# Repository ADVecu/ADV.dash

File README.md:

# ADV.dash

ADV.dash is a dashboard project built with **LVGL** and **ESP32-S3**.  
It is prepared to receive CAN bus data from **rusEFI** and, in the future, other programmable ECUs.

## Requirements
- PlatformIO
- ESP32-S3 DevKitC-1 board (1.5-inch display)
- LVGL library
- rusEFI CAN bus setup

## Compilation Steps
1. Clone the repository:
   ```bash
   git clone https://github.com/ADVecu/ADV.dash.git
   ```
2. Open the project in **PlatformIO**.
3. Copy the file `esp32-s3-devkitc-1-5inch` to the **boards** directory of the **Espressif** platform in PlatformIO.
4. Copy `lv_conf.h` to its correct LVGL configuration folder.
5. Build and upload the project to your ESP32-S3.

## Images

---

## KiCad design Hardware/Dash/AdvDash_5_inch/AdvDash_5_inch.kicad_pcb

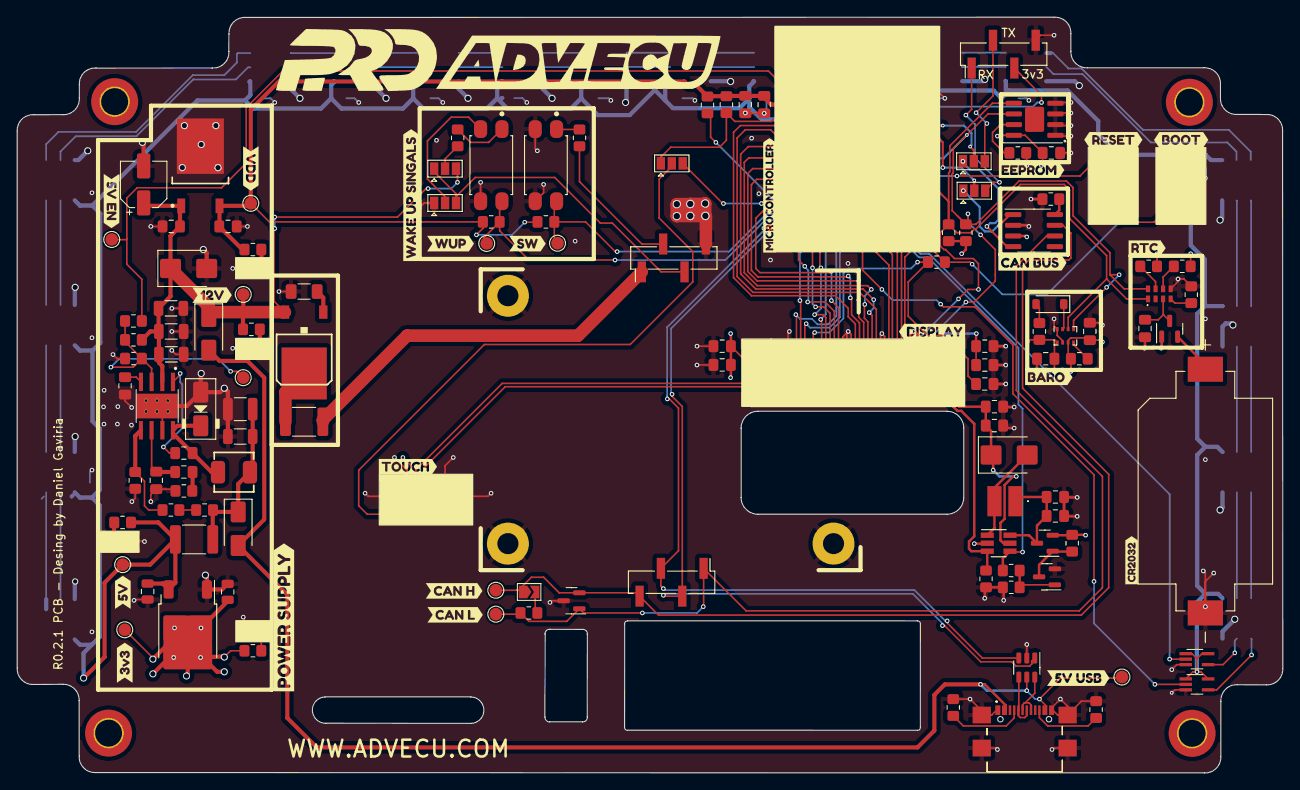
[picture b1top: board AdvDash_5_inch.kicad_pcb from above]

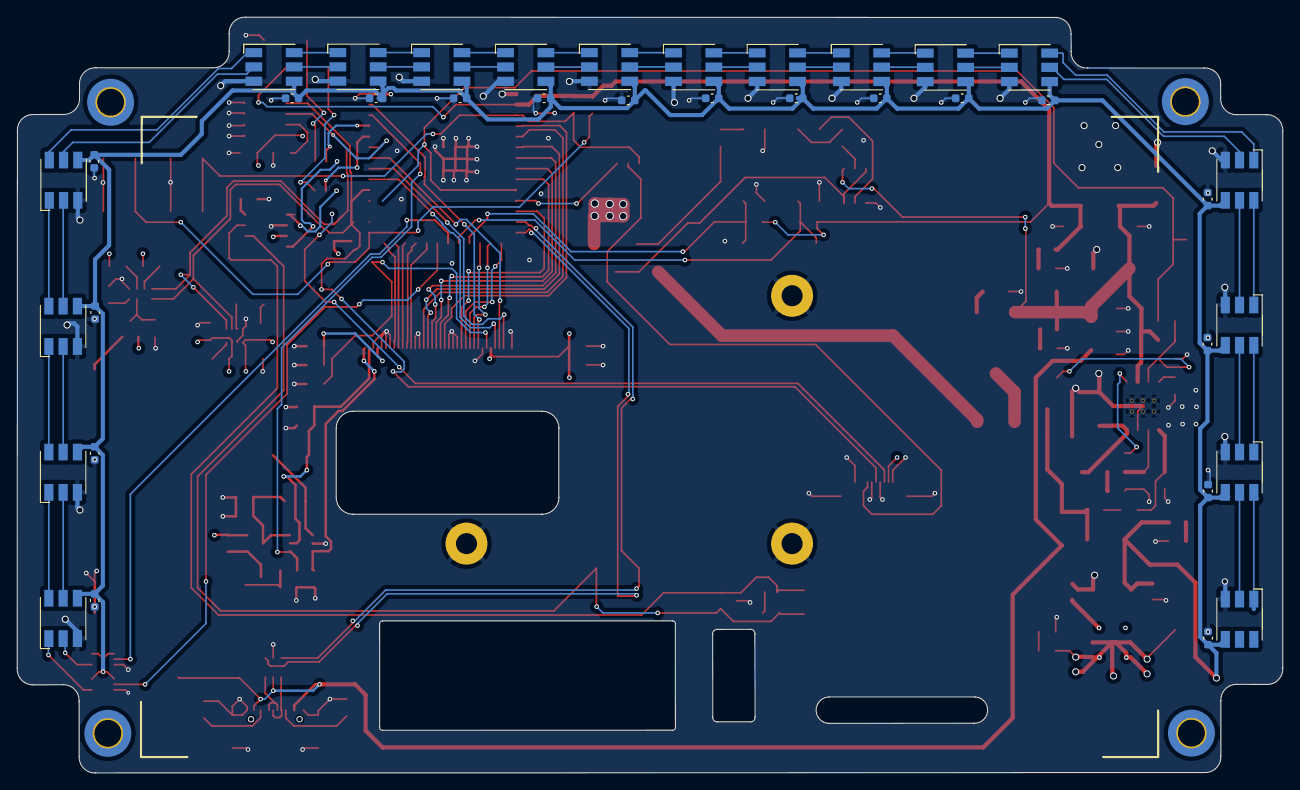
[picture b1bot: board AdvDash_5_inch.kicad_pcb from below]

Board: 4 copper layers, 150.6 x 89.9 mm, 188 parts (36 on the bottom side), 125 nets.

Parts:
BT1: CR2032-BS-6-1; BAT_CR2032-BS-6-1
C1, C7, C12, C21, C23, C27: 0.1uF; C_0805_2012Metric_Pad1.18x1.45mm_HandSolder
C2, C22, C24, C25: 10uF; C_0805_2012Metric_Pad1.18x1.45mm_HandSolder
C3, C4: 4.7uF; C_1206_3216Metric
C5: 10nF; C_1206_3216Metric
C6, C26: 10nF; C_0805_2012Metric_Pad1.18x1.45mm_HandSolder
C8: 4.7nF; C_0805_2012Metric_Pad1.18x1.45mm_HandSolder
C9: 39pF; C_0805_2012Metric_Pad1.18x1.45mm_HandSolder
C10: 33uF; C_1210_3225Metric
C11: 33uF; C_1206_3216Metric
C13: 100nF; CP_Elec_5x5.4
C14: 1uF - X7R; C_0805_2012Metric_Pad1.18x1.45mm_HandSolder
C15, C17: 22uF; C_0805_2012Metric_Pad1.18x1.45mm_HandSolder
C16, C20: 1uF; C_0805_2012Metric_Pad1.18x1.45mm_HandSolder
C18, C19: 100nF; C_0805_2012Metric_Pad1.18x1.45mm_HandSolder
C28, C29: 10uF; C_0805_2012Metric
C30, C31, C32, C33, C34, C35, C36, C37, C38, C39, C40, C41, C42, C43, C44, C45, C46, C47: 0.1uF; C_0603_1608Metric
D1, D11: 1N5819; D_SMA
D2: B340; D_SMA
D3, D4, D6, D12: LED; LED_0805_2012Metric_Pad1.15x1.40mm_HandSolder
D5: SMBJ20A; D_SMB
D7: SS24BF; D_SMB
D8: NUP2105L; SOT-23
D9: 1N4148W; D_SOD-123
D10: BAS70-05; SOT-23
D13, D14, D15, D16, D17, D18, D19, D20, D21, D22, D23, D24, D25, D26, D27, D28, D29, D30: SK9822; LED_RGB_5050-6
F1, F2: 3A 24V; Fuse_1812_4532Metric_Pad1.30x3.40mm_HandSolder
G1: TLF80511TF_V33; INF-PG-TO252-3-11_N
H1, H2, H3, H4: MountingHole; MountingHole_3.2mm_M3_DIN965_Pad_TopBottom
H5, H6, H7: MountingHole_Pad; MountingHole_2.5mm_Pad
IC1: RV-8803-C7; RV8803C7
IC2, IC3: 74HCT1G126GW,125; SOT-353_SC-70-5_Handsoldering
J1: 1-1734839-0; 117348390
J2: 54104-4031
J3: USB4110-GF-A; USB4110GFA
J4, J6: 2.54mm 1x4; PinHeader_1x04_P2.54mm_Vertical_SMD_Pin1Left
J5: UART0; PinHeader_1x04_P2.54mm_Vertical_SMD_Pin1Left
JP1: 120ohm; SolderJumper-2_P1.3mm_Open_TrianglePad1.0x1.5mm
JP2, JP3, JP4, JP6: ACT +/-; SolderJumper-3_P1.3mm_Open_Pad1.0x1.5mm
JP5: Reset Control; SolderJumper-3_P1.3mm_Open_Pad1.0x1.5mm
L1: 6.8uH; MDA4020-6R8M
L2: 6.8uH; TCK145
Q2: AO3401A; SOT-23
Q3: S8050; SOT-23
R1, R2, R7, R12, R17, R24, R26, R27, R35, R36: 10K; R_0805_2012Metric_Pad1.20x1.40mm_HandSolder
R3: 332k; R_0805_2012Metric_Pad1.20x1.40mm_HandSolder
R4: 68k1; R_0805_2012Metric_Pad1.20x1.40mm_HandSolder
R5: 49k9; R_0805_2012Metric_Pad1.20x1.40mm_HandSolder
R6, R10, R21: 0R; R_0805_2012Metric_Pad1.20x1.40mm_HandSolder
R8: 1k91; R_0805_2012Metric_Pad1.20x1.40mm_HandSolder
R9: 2K7; R_1206_3216Metric_Pad1.30x1.75mm_HandSolder
R13, R14: 1k3; R_0805_2012Metric_Pad1.20x1.40mm_HandSolder
R15: 10R; R_0805_2012Metric_Pad1.20x1.40mm_HandSolder
R16, R28, R29, R30, R31: 100k; R_0805_2012Metric_Pad1.20x1.40mm_HandSolder
R18: 100R; R_0805_2012Metric_Pad1.20x1.40mm_HandSolder
R19, R20: 4.7k; R_0805_2012Metric_Pad1.20x1.40mm_HandSolder
R22, R23: 5k1; R_0805_2012Metric_Pad1.20x1.40mm_HandSolder
R25: 120; R_0805_2012Metric_Pad1.20x1.40mm_HandSolder
R32: 2k; R_0805_2012Metric_Pad1.20x1.40mm_HandSolder
R33, R34: 2K7; R_0805_2012Metric_Pad1.20x1.40mm_HandSolder
SW1, SW2: RESET; SW_TL3342F160QG_TR
T1: IRFR5305; D-PAK_TO252AA
TP1: VIN_TP; TestPoint_Pad_D1.5mm
TP2: EN_TP; TestPoint_Pad_D1.5mm
TP3: EN_MCU_TP; TestPoint_Pad_D1.5mm
TP4: USB_5VTP; TestPoint_Pad_D1.5mm
TP5: 5V_TP; TestPoint_Pad_D1.5mm
TP6: VDD_TP; TestPoint_Pad_D1.5mm
TP7: 3.3V_TP; TestPoint_Pad_D1.5mm
TP8: WAKE_UP_TP; TestPoint_Pad_D1.5mm
TP9: SW12V_TP; TestPoint_Pad_D1.5mm
TP10: CANH_TP; TestPoint_Pad_D1.5mm
TP11: CANL_TP; TestPoint_Pad_D1.5mm
U1: ESP32-S3-WROOM-1-N4R8; ESP32-S3-WROOM-1
U2: TPS54331DDA; CONV_TPS54331DDA
U3: MT9201; SOT-23-6_Handsoldering
U4: USBLC6-2P6; SOT-23-6
U5: SN65HVD230; SOIC-8_3.9x4.9mm_P1.27mm
U6: BMP280; Bosch_LGA-8_2x2.5mm_P0.65mm_ClockwisePinNumbering
U7: CAT24C51; SOIC-8-1EP_3.9x4.9mm_P1.27mm_EP2.29x3mm
U8: LD1086DT33TR; TO-252-2
U9, U10: PC817; SOIC254P975X460-4N
kibuzzard-653B3D6F: G***; kibuzzard-653B3D6F
kibuzzard-653B3D82: G***; kibuzzard-653B3D82
kibuzzard-653B3DF4: G***; kibuzzard-653B3DF4
kibuzzard-653B3E73: G***; kibuzzard-653B3E73
kibuzzard-653B3E80: G***; kibuzzard-653B3E80
kibuzzard-653B3ED4: G***; kibuzzard-653B3ED4
kibuzzard-653B3EE1: G***; kibuzzard-653B3EE1
kibuzzard-653B3EFA: G***; kibuzzard-653B3EFA
kibuzzard-653B3F30: G***; kibuzzard-653B3F30
kibuzzard-653B3F43: G***; kibuzzard-653B3F43
kibuzzard-653B3FA3: G***; kibuzzard-653B3FA3
kibuzzard-653B3FD4: G***; kibuzzard-653B3FD4
kibuzzard-653B40B3: G***; kibuzzard-653B40B3
kibuzzard-653B41DD: G***; kibuzzard-653B41DD
kibuzzard-653B42DB: G***; kibuzzard-653B42DB
kibuzzard-653B414E: G***; kibuzzard-653B414E
kibuzzard-653B423C: G***; kibuzzard-653B423C
kibuzzard-653B435E: G***; kibuzzard-653B435E
kibuzzard-653B445A: G***; kibuzzard-653B445A
kibuzzard-653B4004: G***; kibuzzard-653B4004
kibuzzard-653B4099: G***; kibuzzard-653B4099
kibuzzard-653B4196: G***; kibuzzard-653B4196

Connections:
+3.3V: C19.1, C20.1, C22.1, C23.1, C24.1, C25.1, C27.2, C29.1, D10.1 (A2), J1.2, J2.10, J2.37, Q2.2 (S), R13.2, R16.1, R19.1, R20.2, R26.2, R27.2, R29.1, R30.1, TP7.1, U5.3 (VCC), U6.6 (VDDIO), U6.8 (VDD), U7.8 (VCC), U8.2 (OUT)
+5V: C28.1, C30.2, C31.2, C32.2, C33.2, C34.2, C35.2, C36.2, C37.2, C38.2, C39.2, C40.2, C41.2, C42.2, C43.2, C44.2, C45.2, C46.2, C47.2, D13.4 (VCC), D14.4 (VCC), D15.4 (VCC), D16.4 (VCC), D17.4 (VCC), D18.4 (VCC), D19.4 (VCC), D20.4 (VCC), D21.4 (VCC), D22.4 (VCC), D23.4 (VCC), D24.4 (VCC), D25.4 (VCC), D26.4 (VCC), D27.4 (VCC), D28.4 (VCC), D29.4 (VCC), D30.4 (VCC), F1.2, IC2.1 (OE), IC2.5 (VCC), IC3.1 (OE), IC3.5 (VCC), R32.2, TP5.1, U8.3 (IN)
/CAN_H: D8.2 (K), J4.4, JP1.1 (A), TP10.1, U5.7 (CANH)
/CAN_L: D8.1 (K), J4.1, R25.1, TP11.1, U5.6 (CANL)
/Can Bus/CRX: JP4.1 (A), U5.4 (R)
/Can Bus/CTX: JP6.1 (A), U5.1 (D)
/Connector/SW_12V: J6.2, R34.1
/Connector/WAKE_UP: J6.3, JP2.1 (A), JP3.3 (B)
/Display/B3: J2.17, U1.12 (GPIO8/TOUCH8/ADC1_CH7/SUBSPICS1)
/Display/B4: J2.16, U1.15 (GPIO3/TOUCH3/ADC1_CH2)
/Display/B5: J2.15, U1.16 (GPIO46)
/Display/B6: J2.14, U1.17 (GPIO9/TOUCH9/ADC1_CH8/FSPIHD/SUBSPIHD)
/Display/B7: J2.13, U1.39 (GPIO1/TOUCH1/ADC1_CH0)
/Display/DCLK: R2.1, R21.2, SW2.1, SW2.2, U1.27 (GPIO0/BOOT)
/Display/DE: J2.7, U1.33 (MTDO/GPIO40/CLK_OUT2)
/Display/G2: J2.26, U1.5 (GPIO5/TOUCH5/ADC1_CH4)
/Display/G3: J2.25, U1.6 (GPIO6/TOUCH6/ADC1_CH5)
/Display/G4: J2.24, U1.7 (GPIO7/TOUCH7/ADC1_CH6)
/Display/G5: J2.23, U1.8 (GPIO15/U0RTS/ADC2_CH4/XTAL_32K_P)
/Display/G6: J2.22, U1.9 (GPIO16/U0CTS/ADC2_CH5/XTAL_32K_N)
/Display/G7: J2.21, U1.4 (GPIO4/TOUCH4/ADC1_CH3)
/Display/HSYNC: J2.9, U1.32 (MTCK/GPIO39/CLK_OUT3/SUBSPICS1)
/Display/LCD_BL_CTR: R18.1, U1.38 (GPIO2/TOUCH2/ADC1_CH1), U3.4 (EN)
/Display/LCD_LEDA: C17.1, C18.1, D7.1 (K), J2.39, U3.5 (OV)
/Display/LCD_LEDK: J2.40, R15.2, U3.3 (FB)
/Display/R3: J2.33, U1.26 (GPIO45)
/Display/R4: J2.32, U1.25 (GPIO48/SPICLK_N/SUBSPICLK_N_DIFF)
/Display/R5: J2.31, U1.24 (GPIO47/SPICLK_P/SUBSPICLK_P_DIFF)
/Display/R6: J2.30, U1.23 (GPIO21)
/Display/R7: J2.29, U1.22 (GPIO14/TOUCH14/ADC2_CH3/FSPIWP/FSPIDQS/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)
/Display/TP_RST: JP5.1 (A), R1.1, SW1.1, SW1.2, U1.3 (EN)
/Display/TP_RST_2: JP5.3 (B), U1.11 (GPIO18/U1RXD/ADC2_CH7/CLK_OUT3)
/Display/VSYNC: J2.8, U1.34 (MTDI/GPIO41/CLK_OUT1)
/LEDs/WLED_CLK: IC2.2 (A), U1.20 (GPIO12/TOUCH12/ADC2_CH1/FSPICLK/FSPIIO6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)
/LEDs/WLED_CRT: IC3.2 (A), U1.21 (GPIO13/TOUCH13/ADC2_CH2/FSPIQ/FSPIIO7/S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)
/MCU/5V_EN: R10.1, TP3.1, U1.10 (GPIO17/U1TXD/ADC2_CH6)
/MCU/SW_12V: R36.1, TP9.1, U1.18 (GPIO10/TOUCH10/ADC1_CH9/FSPICS0/FSPIIO4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), U10.4
/MCU/U0RXD: J5.1, JP6.3 (B)
/MCU/U0TXD: J5.2, JP4.3 (B)
/MCU/WAKE_UP: R35.1, TP8.1, U1.19 (GPIO11/TOUCH11/ADC2_CH0/FSPID/FSPIIO5/S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), U9.4
/Power Supply/VIN/15_PROT: C3.1, C4.1, C5.1, C12.2, C13.1, D5.1 (K), D11.1 (K), G1.1 (I), JP2.3 (B), R3.1, R12.2, T1.3, TP1.1, U2.2 (VIN)
/SCL: IC1.8 (SCL), J1.3, R19.2, U1.35 (MTMS/GPIO42), U6.4 (SCK), U7.6 (SCL)
/SDA: IC1.1 (SDA), J1.5, R20.1, U1.31 (GPIO38/FSPIWP/SUBSPIWP), U6.3 (SDI), U7.5 (SDA)
/USB5V: D1.2 (A), D11.2 (A), J3.A4 (VBUS), J3.A9 (VBUS), J3.B4 (VBUS), J3.B9 (VBUS), TP4.1, U4.5 (VBUS)
/USBC/D+: J3.A6 (Dp1), J3.B6 (Dp2), J4.2, U1.14 (GPIO20/U1CTS/ADC2_CH9/CLK_OUT1/USB_D+), U4.1 (I/O1), U4.6 (I/O1)
/USBC/D-: J3.A7 (Dn1), J3.B7 (Dn2), J4.3, U1.13 (GPIO19/U1RTS/ADC2_CH8/CLK_OUT2/USB_D-), U4.3 (I/O2), U4.4 (I/O2)
/VIN15: F2.2, J6.1
GND: BT1.N, C1.2, C2.2, C3.2, C4.2, C5.2, C6.2, C9.2, C10.2, C11.2, C12.1, C13.2, C14.2, C15.2, C16.2, C17.2, C18.2, C19.2, C20.2, C21.2, C22.2, C23.2, C24.2, C25.2, C26.2, C27.1, C28.2, C29.2, C30.1, C31.1, C32.1, C33.1, C34.1, C35.1, C36.1, C37.1, C38.1, C39.1, C40.1, C41.1, C42.1, C43.1, C44.1, C45.1, C46.1, C47.1, D2.2 (A), D3.1 (K), D4.1 (K), D5.2 (A), D6.1 (K), D8.3 (A), D12.1 (K), D13.3 (GND), D14.3 (GND), D15.3 (GND), D16.3 (GND), D17.3 (GND), D18.3 (GND), D19.3 (GND), D20.3 (GND), D21.3 (GND), D22.3 (GND), D23.3 (GND), D24.3 (GND), D25.3 (GND), D26.3 (GND), D27.3 (GND), D28.3 (GND), D29.3 (GND), D30.3 (GND), G1.2 (GND), H5.1, H6.1, H7.1, IC1.5 (VSS), IC2.3 (GND), IC3.3 (GND), J1.1, J1.4, J1.6, J1.10, J1.MP1, J1.MP2, J2.5, J2.12, J2.18, J2.19, J2.20, J2.27, J2.28, J2.34, J2.35, J2.36, J2.38, J3.A1 (GND), J3.A12 (GND), J3.B1 (GND), J3.B12 (GND), J3.MP1, J3.MP2, J3.MP3, J3.MP4, J5.4, J6.4, JP3.1 (A), Q3.2 (E), R4.2, R5.2, R8.2, R9.2, R15.1, R17.2, R22.1, R23.2, R24.1, R28.2, R31.2, SW1.3, SW1.4, SW2.3, SW2.4, U1.1 (GND), U1.40 (GND), U1.41 (GND), U2.7 (GND), U2.9 (POWERPAD), U2.10 (GND), U2.11 (GND), U2.12 (GND), U2.13 (GND), U2.14 (GND), U2.15 (GND), U3.2 (GND), U4.2 (GND), U5.2 (GND), U6.1 (GND), U6.7 (GND), U7.1 (A0), U7.2 (A1), U7.3 (A2), U7.4 (GND), U8.1 (ADJ/GND), U9.3, U10.2, U10.3
unnamed: C8.2, R5.1
unnamed: C21.1, J2.11, R21.1
unnamed: C10.1, C11.1, D1.1 (K), F1.1, L1.2, R6.1
unnamed: C7.2, D2.1 (K), L1.1, U2.8 (PH)
unnamed: D3.2 (A), R12.1
unnamed: D4.2 (A), R13.1
unnamed: D6.2 (A), R14.1
unnamed: D7.2 (A), L2.2, U3.1 (SW)
unnamed: D9.2 (A), R26.1
unnamed: D9.1 (K), U6.2 (CSB)
unnamed: BT1.P, D10.2 (A1)
unnamed: C26.1, D10.3 (K), IC1.3 (VDD)
unnamed: D12.2 (A), R32.1
unnamed: D13.2 (CI), IC2.4 (Y)
unnamed: D13.5 (CO), D14.2 (CI)
unnamed: D13.1 (DI), IC3.4 (Y)
unnamed: D13.6 (DO), D14.1 (DI)
unnamed: D14.5 (CO), D15.2 (CI)
unnamed: D14.6 (DO), D15.1 (DI)
unnamed: D15.5 (CO), D16.2 (CI)
unnamed: D15.6 (DO), D16.1 (DI)
unnamed: D16.5 (CO), D17.2 (CI)
unnamed: D16.6 (DO), D17.1 (DI)
unnamed: D17.5 (CO), D18.2 (CI)
unnamed: D17.6 (DO), D18.1 (DI)
unnamed: D18.5 (CO), D19.2 (CI)
unnamed: D18.6 (DO), D19.1 (DI)
unnamed: D19.5 (CO), D20.2 (CI)
unnamed: D19.6 (DO), D20.1 (DI)
unnamed: D20.5 (CO), D21.2 (CI)
unnamed: D20.6 (DO), D21.1 (DI)
unnamed: D21.5 (CO), D22.2 (CI)
unnamed: D21.6 (DO), D22.1 (DI)
unnamed: D22.5 (CO), D23.2 (CI)
unnamed: D22.6 (DO), D23.1 (DI)
unnamed: D23.5 (CO), D24.2 (CI)
unnamed: D23.6 (DO), D24.1 (DI)
unnamed: D24.5 (CO), D25.2 (CI)
unnamed: D24.6 (DO), D25.1 (DI)
unnamed: D25.5 (CO), D26.2 (CI)
unnamed: D25.6 (DO), D26.1 (DI)
unnamed: D26.5 (CO), D27.2 (CI)
unnamed: D26.6 (DO), D27.1 (DI)
unnamed: D27.5 (CO), D28.2 (CI)
unnamed: D27.6 (DO), D28.1 (DI)
unnamed: D28.5 (CO), D29.2 (CI)
unnamed: D28.6 (DO), D29.1 (DI)
unnamed: D29.5 (CO), D30.2 (CI)
unnamed: D29.6 (DO), D30.1 (DI)
unnamed: F2.1, T1.4
unnamed: IC1.4 (CLKOE), R28.1
unnamed: IC1.7 (EVI), R29.2
unnamed: IC1.6 (~INT), R30.2
unnamed: J3.A5 (CC1), R22.2
unnamed: J3.B5 (CC2), R23.1
unnamed: JP1.2 (B), R25.2
unnamed: JP2.2 (C), R33.1
unnamed: JP3.2 (C), U9.2
unnamed: JP4.2 (C), U1.37 (U0TXD/GPIO43/CLK_OUT1)
unnamed: J1.7, JP5.2 (C)
unnamed: JP6.2 (C), U1.36 (U0RXD/GPIO44/CLK_OUT2)
unnamed: C15.1, C16.1, L2.1, Q2.3 (D), U3.6 (VIN)
unnamed: Q2.1 (G), Q3.3 (C), R16.2
unnamed: Q3.1 (B), R17.1, R18.2
unnamed: R6.2, R7.1
unnamed: R9.1, T1.1
unnamed: R33.2, U9.1
unnamed: R34.2, U10.1
unnamed: C7.1, U2.1 (BOOT)
unnamed: C8.1, C9.1, U2.6 (COMP)
unnamed: R3.2, R4.1, R10.2, TP2.1, U2.3 (EN)
unnamed: C6.1, U2.4 (SS)
unnamed: R7.2, R8.1, U2.5 (VSENSE)
unnamed: R24.2, U5.8 (Rs)
unnamed: R27.1, U6.5 (SDO)
unnamed: R31.1, U7.7 (WP)
VDD: C1.1, C2.1, C14.1, G1.3 (Q), J5.3, R1.2, R2.2, R14.2, R35.2, R36.2, TP6.1, U1.2 (3V3)

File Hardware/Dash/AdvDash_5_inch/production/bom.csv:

Designator,Footprint,Quantity,Value,LCSC Part #
BT1,BAT_CR2032-BS-6-1,1,CR2032-BS-6-1,C70377
"C1, C12, C21, C23, C27, C7",0805,6,0.1uF,C38141
C10,1210,1,33uF,C531418
C11,1206,1,33uF,C342606
C13,CP_Elec_5x5.4,1,100nF,C2992591
C14,0805,1,1uF - X7R,C116352
"C15, C17",0805,2,22uF,C602037
"C16, C20",0805,2,1uF,C28323
"C18, C19",0805,2,100nF,C38141
"C2, C22, C24, C25",0805,4,10uF,C15850
"C26, C6",0805,2,10nF,C83170
"C28, C29",0805,2,10uF,C1713
"C3, C4",1206,2,4.7uF,C1872
"C30, C31, C32, C33, C34, C35, C36, C37, C38, C39, C40, C41, C42, C43, C44, C45, C46, C47",0603,18,0.1uF,C577419
C5,1206,1,10nF,C106239
C8,0805,1,4.7nF,C1744
C9,0805,1,39pF,C1817
"D1, D11",D_SMA,2,1N5819,C437199
D10,SOT-23,1,BAS70-05,C5189799
D12,0805,1,LED,C965819
"D13, D14, D15, D16, D17, D18, D19, D20, D21, D22, D23, D24, D25, D26, D27, D28, D29, D30",LED_RGB_5050-6,18,SK9822,C2829089
D2,D_SMA,1,B340,C64982
"D3, D4",0805,2,LED,C965818
D5,D_SMB,1,SMBJ20A,C151257
D6,0805,1,LED,C965812
D7,D_SMB,1,SS24BF,C35501
D8,SOT-23,1,NUP2105L,C5158054
D9,D_SOD-123,1,1N4148W,C5345962
"F1, F2",1812,2,3A 24V,C883154
G1,INF-PG-TO252-3-11_N,1,TLF80511TF_V33,
"H1, H2, H3, H4",MountingHole_3.2mm_M3_DIN965_Pad_TopBottom,4,MountingHole,
"H5, H6, H7",MountingHole_2.5mm_Pad,3,MountingHole_Pad,C3020128
IC1,RV8803C7,1,RV-8803-C7,C2846926
"IC2, IC3",SOT-353_SC-70-5_Handsoldering,2,"74HCT1G126GW,125",C455064
J1,117348390,1,1-1734839-0,C590935
J2,54104-4031,1,54104-4031,C164172
J3,USB4110GFA,1,USB4110-GF-A,
"J4, J6",PinHeader_1x04_P2.54mm_Vertical_SMD_Pin1Left,2,2.54mm 1x4,
J5,PinHeader_1x04_P2.54mm_Vertical_SMD_Pin1Left,1,UART0,
JP1,SolderJumper-2_P1.3mm_Open_TrianglePad1.0x1.5mm,1,120ohm,
"JP2, JP3, JP4, JP6",SolderJumper-3_P1.3mm_Open_Pad1.0x1.5mm,4,ACT +/-,
JP5,SolderJumper-3_P1.3mm_Open_Pad1.0x1.5mm,1,Reset Control,
L1,MDA4020-6R8M,1,6.8uH,C2847472
L2,TCK145,1,6.8uH,C167253
Q2,SOT-23,1,AO3401A,C15127
Q3,SOT-23,1,S8050,C266592
"R1, R12, R17, R2, R24, R26, R27, R35, R36, R7",0805,10,10K,C17414
R10,0805,1,0R,C17414
"R13, R14",0805,2,1k3,C2933303
R15,0805,1,10R,C25278
"R16, R28, R29, R30, R31",0805,5,100k,C149504
R18,0805,1,100R,C17408
"R19, R20",0805,2,4.7k,C17673
"R21, R6",0805,2,0R,C17477
"R22, R23",0805,2,5k1,C84375
R25,0805,1,120,C114245
R3,0805,1,332k,C212383
R32,0805,1,2k,C17604
"R33, R34",0805,2,2K7,C17530
R4,0805,1,68k1,C5266070
R5,0805,1,49k9,C17719
R8,0805,1,1k91,C2999452
R9,1206,1,2K7,C2907449
"SW1, SW2",SW_TL3342F160QG_TR,2,RESET,C2886898
T1,D-PAK_TO252AA,1,IRFR5305,C5155388
TP1,TestPoint_Pad_D1.5mm,1,VIN_TP,
TP10,TestPoint_Pad_D1.5mm,1,CANH_TP,
TP11,TestPoint_Pad_D1.5mm,1,CANL_TP,
TP2,TestPoint_Pad_D1.5mm,1,EN_TP,
TP3,TestPoint_Pad_D1.5mm,1,EN_MCU_TP,
TP4,TestPoint_Pad_D1.5mm,1,USB_5VTP,
TP5,TestPoint_Pad_D1.5mm,1,5V_TP,
TP6,TestPoint_Pad_D1.5mm,1,VDD_TP,
TP7,TestPoint_Pad_D1.5mm,1,3.3V_TP,
TP8,TestPoint_Pad_D1.5mm,1,WAKE_UP_TP,
TP9,TestPoint_Pad_D1.5mm,1,SW12V_TP,
U1,ESP32-S3-WROOM-1,1,ESP32-S3-WROOM-1-N4R8,C2913200
"U10, U9",SOIC254P975X460-4N,2,PC817,C3025164
U2,CONV_TPS54331DDA,1,TPS54331DDA,C90761
U3,SOT-23-6_Handsoldering,1,MT9201,C182966
U4,SOT-23-6,1,USBLC6-2P6,C7519
U5,SOIC-8_3.9x4.9mm_P1.27mm,1,SN65HVD230,C12084
U6,Bosch_LGA-8_2x2.5mm_P0.65mm_ClockwisePinNumbering,1,BMP280,C83291
U7,SOIC-8-1EP_3.9x4.9mm_P1.27mm_EP2.29x3mm,1,CAT24C51,C79986
U8,TO-252-2,1,LD1086DT33TR,C12051

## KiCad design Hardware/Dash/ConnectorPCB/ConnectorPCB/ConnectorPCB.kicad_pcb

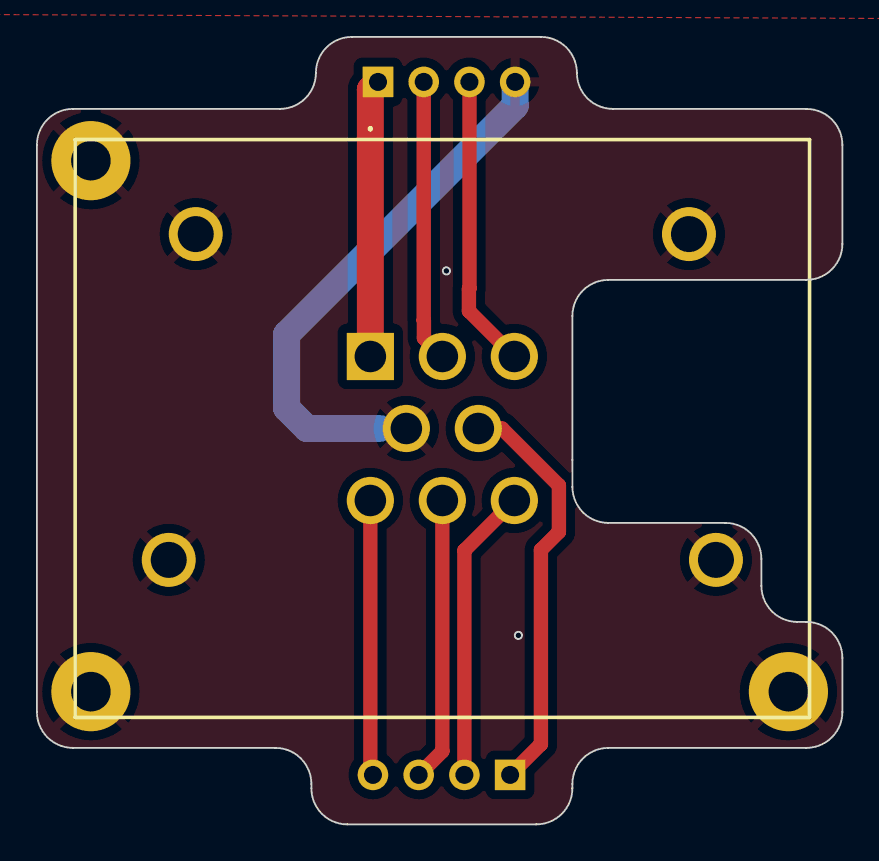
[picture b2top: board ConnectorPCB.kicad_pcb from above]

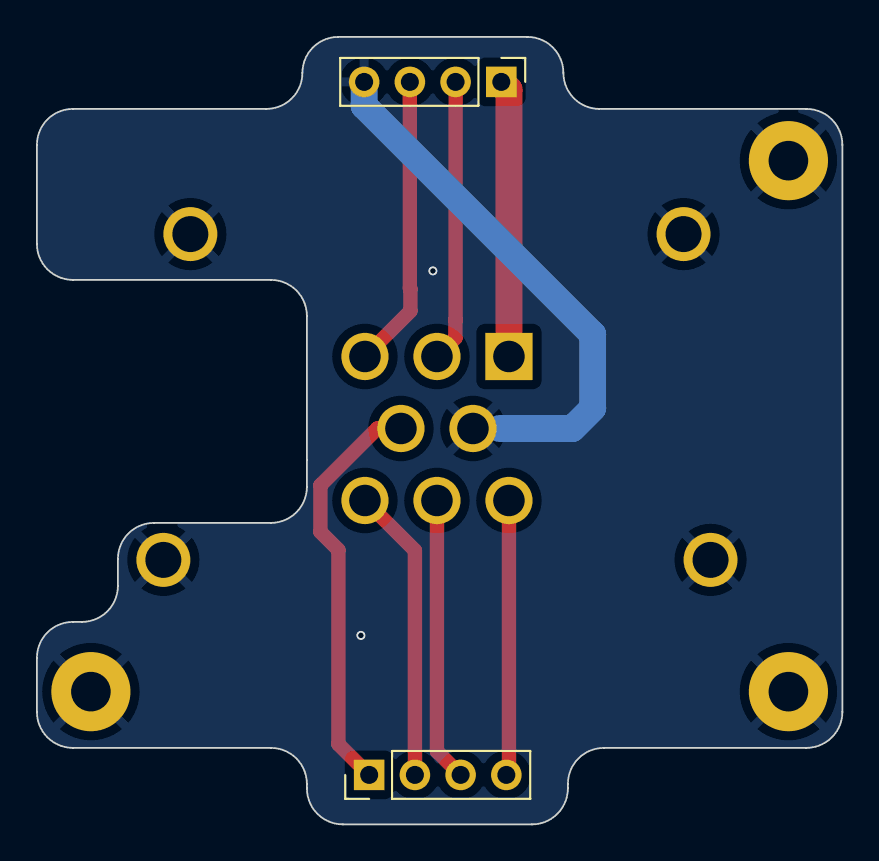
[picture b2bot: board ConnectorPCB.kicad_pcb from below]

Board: 2 copper layers, 44.8 x 43.8 mm, 4 parts (2 on the bottom side), 8 nets.

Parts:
H5: MountingHole_Pad; MountingHole_2.2mm_M2_Pad
J1: 776276-1; 7762761
J2, J3: 2.54mm 1x4; PinHeader_1x04_P2.54mm_Vertical

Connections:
CAN_H: J1.6, J3.4
CAN_L: J1.5, J3.1
D+: J1.7, J3.3
D-: J1.8, J3.2
GND: H5.1, J1.4, J1.MH1, J1.MH2, J1.MH3, J1.MH4, J2.4
SW_12V: J1.2, J2.2
VIN/15V: J1.1, J2.1
WAKE_UP: J1.3, J2.3

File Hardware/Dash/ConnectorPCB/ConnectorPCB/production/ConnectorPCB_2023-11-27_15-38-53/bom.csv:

Designator,Footprint,Quantity,Value,LCSC Part #
J1,7762761,1,776276-1,
"J2, J3",PinHeader_1x04_P2.54mm_Vertical,2,2.54mm 1x4,

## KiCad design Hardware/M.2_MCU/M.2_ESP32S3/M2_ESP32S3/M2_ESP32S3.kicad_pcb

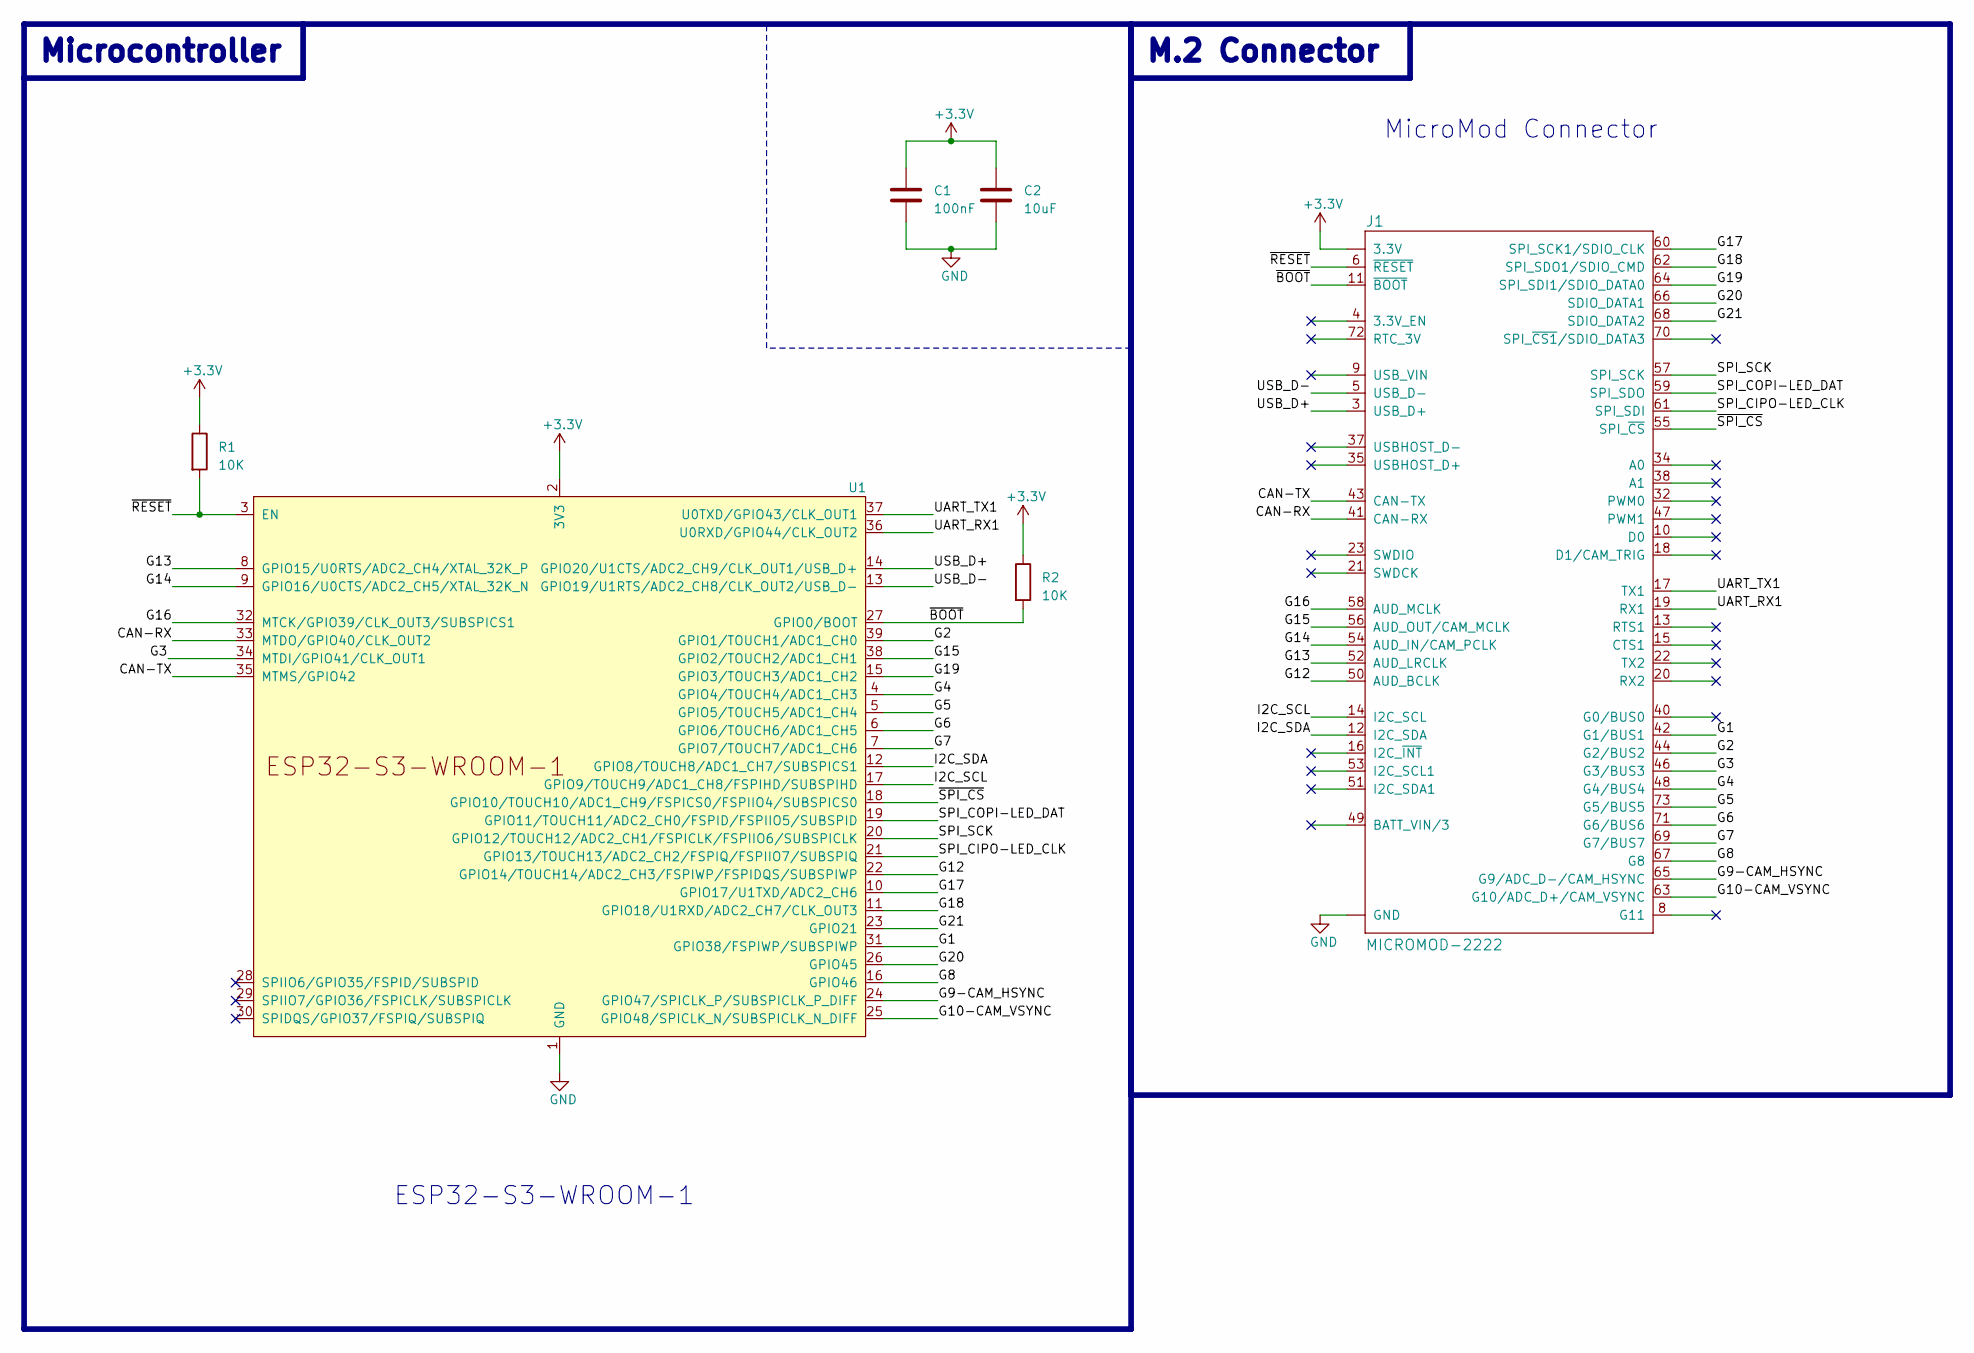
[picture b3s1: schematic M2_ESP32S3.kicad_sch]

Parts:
C1: 100nF; C_0805_2012Metric_Pad1.18x1.45mm_HandSolder
C2: 10uF; C_0805_2012Metric_Pad1.18x1.45mm_HandSolder
J1: MICROMOD-2222; M.2-CARD-E-22
R1, R2: 10K; R_0805_2012Metric_Pad1.15x1.40mm_HandSolder
U1: ESP32-S3-WROOM-1

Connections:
+3.3V: C1.1, C2.1, J1.2 (3.3V), J1.74 (3.3V), R1.1, R2.1, U1.2 (3V3)
/CAN-RX: J1.41 (CAN-RX), U1.33 (MTDO/GPIO40/CLK_OUT2)
/CAN-TX: J1.43 (CAN-TX), U1.35 (MTMS/GPIO42)
/G1: J1.42 (G1/BUS1), U1.31 (GPIO38/FSPIWP/SUBSPIWP)
/G2: J1.44 (G2/BUS2), U1.39 (GPIO1/TOUCH1/ADC1_CH0)
/G3: J1.46 (G3/BUS3), U1.34 (MTDI/GPIO41/CLK_OUT1)
/G4: J1.48 (G4/BUS4), U1.4 (GPIO4/TOUCH4/ADC1_CH3)
/G5: J1.73 (G5/BUS5), U1.5 (GPIO5/TOUCH5/ADC1_CH4)
/G6: J1.71 (G6/BUS6), U1.6 (GPIO6/TOUCH6/ADC1_CH5)
/G7: J1.69 (G7/BUS7), U1.7 (GPIO7/TOUCH7/ADC1_CH6)
/G8: J1.67 (G8), U1.16 (GPIO46)
/G9-CAM_HSYNC: J1.65 (G9/ADC_D-/CAM_HSYNC), U1.24 (GPIO47/SPICLK_P/SUBSPICLK_P_DIFF)
/G10-CAM_VSYNC: J1.63 (G10/ADC_D+/CAM_VSYNC), U1.25 (GPIO48/SPICLK_N/SUBSPICLK_N_DIFF)
/G12: J1.50 (AUD_BCLK), U1.22 (GPIO14/TOUCH14/ADC2_CH3/FSPIWP/FSPIDQS/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)
/G13: J1.52 (AUD_LRCLK), U1.8 (GPIO15/U0RTS/ADC2_CH4/XTAL_32K_P)
/G14: J1.54 (AUD_IN/CAM_PCLK), U1.9 (GPIO16/U0CTS/ADC2_CH5/XTAL_32K_N)
/G15: J1.56 (AUD_OUT/CAM_MCLK), U1.38 (GPIO2/TOUCH2/ADC1_CH1)
/G16: J1.58 (AUD_MCLK), U1.32 (MTCK/GPIO39/CLK_OUT3/SUBSPICS1)
/G17: J1.60 (SPI_SCK1/SDIO_CLK), U1.10 (GPIO17/U1TXD/ADC2_CH6)
/G18: J1.62 (SPI_SDO1/SDIO_CMD), U1.11 (GPIO18/U1RXD/ADC2_CH7/CLK_OUT3)
/G19: J1.64 (SPI_SDI1/SDIO_DATA0), U1.15 (GPIO3/TOUCH3/ADC1_CH2)
/G20: J1.66 (SDIO_DATA1), U1.26 (GPIO45)
/G21: J1.68 (SDIO_DATA2), U1.23 (GPIO21)
/I2C_SCL: J1.14 (I2C_SCL), U1.17 (GPIO9/TOUCH9/ADC1_CH8/FSPIHD/SUBSPIHD)
/I2C_SDA: J1.12 (I2C_SDA), U1.12 (GPIO8/TOUCH8/ADC1_CH7/SUBSPICS1)
/SPI_CIPO-LED_CLK: J1.61 (SPI_SDI), U1.21 (GPIO13/TOUCH13/ADC2_CH2/FSPIQ/FSPIIO7/S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)
/SPI_COPI-LED_DAT: J1.59 (SPI_SDO), U1.19 (GPIO11/TOUCH11/ADC2_CH0/FSPID/FSPIIO5/S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)
/SPI_SCK: J1.57 (SPI_SCK), U1.20 (GPIO12/TOUCH12/ADC2_CH1/FSPICLK/FSPIIO6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)
/UART_RX1: J1.19 (RX1), U1.36 (U0RXD/GPIO44/CLK_OUT2)
/UART_TX1: J1.17 (TX1), U1.37 (U0TXD/GPIO43/CLK_OUT1)
/USB_D+: J1.3 (USB_D+), U1.14 (GPIO20/U1CTS/ADC2_CH9/CLK_OUT1/USB_D+)
/USB_D-: J1.5 (USB_D-), U1.13 (GPIO19/U1RTS/ADC2_CH8/CLK_OUT2/USB_D-)
/~BOOT: J1.11 (~BOOT), R2.2, U1.27 (GPIO0/BOOT)
/~RESET: J1.6 (~RESET), R1.2, U1.3 (EN)
/~SPI_CS: J1.55 (SPI_~CS), U1.18 (GPIO10/TOUCH10/ADC1_CH9/FSPICS0/FSPIIO4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)
GND: C1.2, C2.2, J1.1 (GND), J1.7 (GND), J1.33 (GND), J1.36 (GND), J1.39 (GND), J1.45 (GND), J1.75 (GND), J1.GND1 (GND), J1.GND2 (GND), J1.GND3 (GND), U1.1 (GND), U1.40 (GND), U1.41 (GND)

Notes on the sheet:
Microcontroller
ESP32-S3-WROOM-1
MicroMod Connector
M.2 Connector

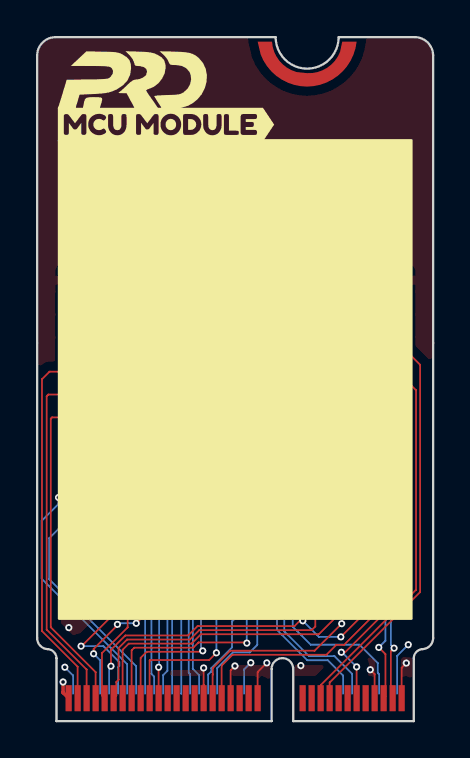
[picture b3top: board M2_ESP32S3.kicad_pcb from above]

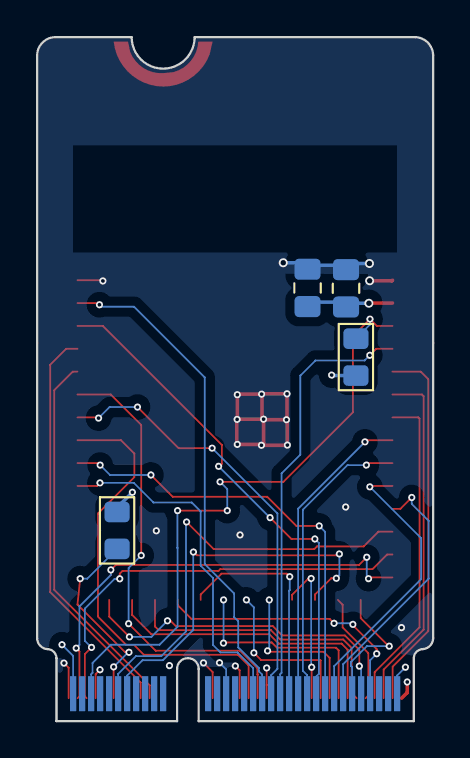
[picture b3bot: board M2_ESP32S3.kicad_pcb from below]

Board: 4 copper layers, 22.0 x 38.0 mm, 9 parts (4 on the bottom side), 36 nets.

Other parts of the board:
FRAME1: FRAME-LEDGER; CREATIVE_COMMONS
LOGO1: SPECIAL_INSTRUCTIONS-ORDERING; ORDERING_INSTRUCTIONS
kibuzzard-652F57BF: G***; kibuzzard-652F57BF

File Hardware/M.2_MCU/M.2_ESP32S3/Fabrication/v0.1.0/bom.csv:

Designator,Footprint,Quantity,Value,LCSC Part #
C1,0805,1,100nF,
C2,0805,1,10uF,
FRAME1,CREATIVE_COMMONS,1,FRAME-LEDGER,
J1,M.2-CARD-E-22,1,MICROMOD-2222,
LOGO1,ORDERING_INSTRUCTIONS,1,SPECIAL_INSTRUCTIONS-ORDERING,
"R1, R2",0805,2,10K,
U1,ESP32-S3-WROOM-1,1,ESP32-S3-WROOM-1,
kibuzzard-652F57BF,kibuzzard-652F57BF,1,G***,

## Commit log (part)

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2023-09-16 Firts commit
2023-09-16 Firts commit 2
2023-09-16 add README.d file
2023-09-17 add arcs gauges and firts performance test whit ramdom numbers
2023-09-18 add Screen 2 + first test of charts
2023-09-27 can bus, database, ui control classes implementations
2023-09-27 First implementations of the project structure
2023-09-28 CanBus logic firts prototipe OK
2023-09-29 Trace Log filter
2023-09-29 xQueue for send data from Can Bus to ui control
2023-09-29 Bar widget class contructor implementation
2023-09-30 Bar Gauge class implementation 80%
2023-10-01 Assigning the value of the bars through the iteration of an array
2023-10-03 Arc Gauge Class Working
2023-10-04 RPMS bar issue #2 corrected, panels and tps bar classes ok
2023-10-04 Doxigen Documentation added, more elegant css styles for the doxygen html output
2023-10-09 Settings page first implementations
2023-10-10 Add Units panel in the settings screen
2023-10-10 Arcs logic added to settings screen, unit manager implementation firts test
2023-10-12 Add blue section to the arc and bar BG, fix the numbers of the rpm bar BG
2023-10-12 Add restore default BTN
2023-10-12 Add common LVGL words to grammar ext
2023-10-12 Save Settings BTN working, long press for reset and restore defaults
2023-10-19 Hardware directory added
2023-10-27 R0.1.0 PCB added
2023-11-01 PCB R0.1.0
2023-11-01 Backlink to CADLAB.io has been added.
2023-12-26 :white_check_mark: Add STL files and some renders off the of the casing
2023-12-26 :adhesive_bandage: Minor change to the PCB
2023-12-26 :alembic: Code for testing new PCBs
2023-12-28 :adhesive_bandage: Fix errors in pcb desing, changelog in file, rev0.2.0
2023-12-28 :white_check_mark: Dxf files for acrilic parts, new case top part
2023-12-28 :art: Introduce pcb definition file, clean up in main.c
2023-12-30 :sparkles: RGB leds control added, leds welcome animation logic complete
2023-12-31 :see_no_evil: Add kicad backups to git ignore
2023-12-31 :sparkles: New fastled library, new welcome animation, trigger welcome animation posible at any time
2023-12-31 :art: Improve pcb definitions to work whit 7 inch board
2024-01-02 :lipstick: More resolution added to rmps bar to add smooth movement
2024-01-02 :sparkles: Rpms leds now working
2024-01-02 :children_crossing: More brightness for the LEDs
2024-01-02 :heavy_plus_sign: These 2 files are necessary for the platformio project to work
2024-01-02 :loud_sound: Now if there is any error in the can driver it prints it in the Serial Console
2024-01-02 :art: More pcb specific definitions, LEDs related
2024-01-02 :wastebasket: More kicad stuff to be deleted
2024-01-03 :alembic: Firts test of control logic for indicators leds
2024-01-03 :alembic: [TEST] Funtion to control indicators Leds
2024-01-03 :art: [ADD] Definitions related to indicator leds, new enums for indicador leds control
2024-01-07 :fire: More Kicad stuff deleted
2024-01-07 :bug: PCB R0.2.0 Ready, change log in kicad files
2024-01-07 :arrow_up: Change Fastled library to test more stable library on esp32
2024-01-07 :see_no_evil: Ignore VSCODE settings file
2024-01-07 :construction: Leds control now whit FreeRTOS tasks
2024-02-04 :bug: [FIX] Solution to several errors in the pcb design, log of changes in kicad files
2024-02-04 :bug: [FIX] Added space to access the display connector without desoldering the main connector
2024-02-04 :lipstick: [UI] New welcome screen, changes to the main screen, it now has 3 buttons, new panel with time and temperature information
2024-02-04 :lipstick: [UI] New changes in UI generated automatically
2024-02-04 :zap: [CANBUS] Change in data sent to queue, fuel data is removed
2024-02-04 :poop: Many Changes and performance test
2024-02-04 :zap: [FIX] LED replacement for SK9822 due to poor performance with only 1 data line
2024-02-04 :recycle: [MOD] Change gauge defaults for panels
2024-02-04 :recycle: [MOD] Change in loop and setup functions
2024-02-04 :sparkles: [ADD] New pcb options for LEDs and Sleep functions
2024-02-04 :bug: [FIX] New i2c pins for new board
2024-02-04 :lipstick: [ADD] New UI images
2024-02-04 :sparkles: [ADD] RTC control added and working
2024-02-04 :sparkles: [ADD] Atmosferic atmospheric pressure and temperature data added (BMP180)
2024-02-04 :poop: For now only for test
2024-02-04 :bookmark: [PCB] Main PCB R0.2.0
2024-02-04 :pencil2: Vscode settings
2024-02-04 :bug: [FIX] Change some convertions values
2024-02-04 :zap: [FIX] Delete condition on main canbus loop
2024-02-04 :sparkles: [ADD] Canbus data factor correction to show correct values
2024-02-04 :bug: [FIX] New defaults and alerts for corrected canbus values
2024-02-04 :white_check_mark: Active LEDs for performance testing
2024-03-17 :poop: Development is resumed after a long time, I have no idea what was modified before, let's hope for the best, last change, now in the time and date a 0 was added at the beginning if the number i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
2024-04-05 :fire: Remove Squereline backups?
2024-04-05 :art: Minor Change UI Export from Squereline
2024-04-05 :bug: [FIX] TPS value in canbus_data_t was uint_8, change for uint_16
2024-04-05 :zap: [FIX] Read a value from Flash is quite slow, change to read values from RAM
2024-04-05 :bug: [FIX] Alerts colors now working, AFR gauge new look
2024-04-05 :bug: [FIX] Battery Bar Colors fix, tps bar FIX
2024-04-05 :pencil2: [FIX] New AFR gauge defaults
2024-04-05 :zap: [FIX] Now the backlight only turn on at the end of setup
2024-04-05 :art: New GitIgnore
2024-04-06 :art: [NEW] Now each gauge type saves its alerts independently
2024-04-06 :art: [FIX] Changes to implement the new database structure
2024-04-07 :sparkles: New Alert manager implementation tested OK
2024-04-07 :poop: Testing new values for led control, not working
2024-04-10 Add alert manager data to the database
2024-04-10 ➕ Add Queue library as a dependency
2024-04-14 ➕ Add UI control header to alert_manager.h
2024-04-14 🎨 Refactor database.cpp to add vscode minimap new sections
2024-04-15 Update Queue library dependency to CircularBuffer
2024-04-15 some random stuff from vscode
2024-04-15 ✨ Refactor alert_manager.cpp and alert_manager.h to improve alert handling, not tested
2024-04-16 🐛 Refactor can_bus.cpp to handle temperature values within a specific range
2024-04-16 🐛 Refactor alert_manager.cpp to fix alert calculations and display values in criticalPanel
2024-04-16 ♻️ change default value for FUEL_PRESSURE_LOW_ALERT in database.h
2024-04-22 ➕ Add FastCRC library as a dependency
2024-04-22 ✨ Add new files for TunerStudio functionality
2024-04-22 ✨ Add TS ini file
2024-04-22 ✏️ Fix typo in database.cpp comments
2024-04-23 🩹 turn off serial debug for can bus comms
2024-04-23 💩 TS test port causes reset
2024-04-23 🚧 Add SerialCommsInit() function call in setup() to initialize serial communication
2024-04-23 🚧 Work in Progress
2024-04-28 🗑️ Removed control section from configuration page
2024-04-28 🎨 Update PCB pin assignments and configuration in main.cpp and pcb_definitions.h
2024-04-28 ✨ Update PCB pin assignments and configuration for ADVdash7inchV2SD in pcb_definitions.h
2024-04-28 💄 Change to the Settings UI
2024-04-28 💩 Fix typo in codeVersion array initialization
2024-04-28 🤡 TS communication protocol is complicated
2024-04-28 ✏️ Fix typo in ADVdashDev.ini
2024-04-28 ♻️ In case I regret it later
2024-04-29 🐛 Update TOUCH_MAP_X2 for correct touch calibration
2024-04-29 ♻️ Update PCB configuration for ADVdash5inch in
2024-04-29 ♻️ 255 backlight for 5 inch
2024-04-29 ➕ More Stuff
2024-04-29 ✨ Refactor gp_arc class to change user setting on the go
2024-04-29 🚧 Now the user settings happen in the main screen
2024-04-29 ✨ New Settings logic testing
2024-04-29 💄 New user settings UI
2024-04-30 💄 Now, config panel show in the correct place
2024-04-30 ✨ Add gearPanel and speedPanel classes for UI control widgets
2024-04-30 💄 UI events for Config Panel
2024-04-30 ✨ Add speedPanel and gearPanel Control
2024-04-30 🚧 New config manager code
2024-06-15 🎨 Refactor code to improve readability and remove unnecessary comments
2024-06-15 🚀 PCB R0.2.1
2024-06-15 🎨 Refactor PCB definitions file
2024-06-15 💄 New Features Test
2024-06-15 💄 Refactor UI code to add oil press image and container
2024-06-16 ✨ New CanBus DBC with PRO Frames
2024-06-16 ✨ New CanBus Messages Added, Debug Prints with macros
2024-06-16 🐛 Added Macro pdMS_TO_TICKS for the queue wait time
2024-06-16 🐛 Fix led logic remove data from the queue before uicontrol, change to xQueuePeek
2024-06-22 ⚡️ Time to wait for CanBus Frame changed to 0
2024-06-22 ✨ Add menu button messages to Can Database
2024-06-30 ✨ Update rus_efi_can_verbose.c with new pack and unpack functions
2024-06-30 💄 New Left menu and trip info section
2024-06-30 ✨ Add new CAN messages and update CAN data struct
2024-06-30 ✨ Add menu button logic and menu manager file
2024-06-30 💄 New menu for user, new trip info window
2024-06-30 ✨ Add menu manager and keypad functionality
2024-09-22 New CAD desing for Bike
2024-09-22 Add new CAN messages and update CAN data struct
2024-09-22 Small Change in kicad Files
2024-09-22 Change in UI, NO SURE WHY?
2024-09-22 Add EEPROM manager for handling external EEPROM memory
2024-09-22 Refactor UI control code and add EEPROM manager
    - Refactor the UI control code to enable alerts via the user interface.
    - Add EEPROM manager for handling external EEPROM memory.
2024-09-22 ✨ Refactor UI control code and add EEPROM manager
2024-09-22 ♻️ Refactor UI control code and add EEPROM manager
2024-09-23 🐛 Change in menu BTS
2024-09-25 ♻️ change rpms range for leds
2024-09-25 ✨ New Frame for Gateway data from dashController
2024-09-25 Add 12V and WakeUp switch pin modes in setup()
2024-09-25 ✨ New Sensor, Ambient Temperature Added
2024-09-26 ✨ LuaScript file for dashController
2024-09-26 ✨ Oil Temperature can bus data
2024-09-27 ✨ Digital Inputs Data
2024-09-27 🐛 Lua Progress
2024-09-27 ⚡️ QS Lua
2024-09-27 ⚡️ Refactor LED control code to use FastLED library
2024-09-27 Refactor LED control code to disable FastLED interrupts
2024-09-27 ♻️ Refactor QS Lua and LED control code
    - In TT250Lua.txt, invert the value of qsTimingAdd setting
    - In TT250Lua.txt, divide qsDuration by 1000
    - In led_control.cpp, change the priority of ledControlTask and ShowRunnerTask to 2
2024-09-28 🚧 Side leds disable for now
2024-09-28 ✨ Introduce Dash Icons
2024-09-28 🤡 To Big PNG files
2024-09-28 ✨ Introduce Dash Icons widget and refactor LED control code
2024-09-28 ✨ Add new fields to canbus_data struct
2024-09-28 💄 500 ms Turn signals blink
2024-09-28 ✨ FogLight manager
2024-09-28 💄 Left Arrow Location
2024-09-28 ⚡️ Refactor data rate cycle triggers in ui_control.cpp
2024-09-28 🚧 Simpler Screen manager for now
2024-09-28 ♻️ Added former screen manager
2024-09-29 🚧 Work in progrees sleep mode
2024-09-29 ✨ Send keep alive frame in can_bus.cpp
2024-09-29 🐛 Error Fix, Crash at boot
2024-09-29 ⚡️ New timer for icons data rate, Revert change in main data rate
2024-09-29 💄 Show coolant icon at startup
2024-09-29 ✨ Add fuel trim, fuel flow, and fuel used data to canbus_read function
2024-09-29 ✨ Add support for new gauge types in UI control
2024-09-29 💄 Change in final Screen
2024-09-29 ✨ Add support for tire pressure in canbus_encode struct
2024-09-30 Fix tire pressure display precision in gp_panel widget
2024-09-30 Fix tire pressure display precision in canbus_encode struct
2024-09-30 🐛 Fix out-of-range value in tpsBar::setValue function
2024-09-30 🐛 Fix tire pressure display precision in canbus_encode struct
2024-09-30 ⚡️ Update data rate thresholds in ui_task function
2024-09-30 💄 Fuel used display precision Liters
2025-08-10 Refactor gp_panel.cpp and update KiCad project settings
    Removed unnecessary whitespace and improved formatting in gp_panel.cpp. Updated fuel used calculation logic. Added new DRC and BOM settings to AdvDash_5_inch.kicad_pro. Updated .gitignore to exclude 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

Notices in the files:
parts and their libraries:
https://creativecommons.org/licenses/by-sa/4.0
Released under the Creative Commons Attribution Share-Alike 4.0 License
